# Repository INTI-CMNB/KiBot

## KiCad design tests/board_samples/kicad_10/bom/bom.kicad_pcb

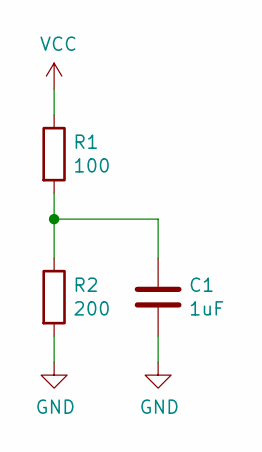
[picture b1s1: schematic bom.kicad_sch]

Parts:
C1: 1uF; C_0805_2012Metric
R1: 100; R_0805_2012Metric
R2: 200; R_0805_2012Metric

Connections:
GND: C1.2, R2.2
unnamed: C1.1, R1.2, R2.1
VCC: R1.1

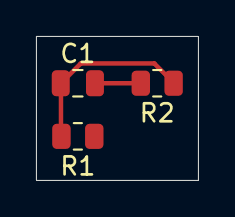
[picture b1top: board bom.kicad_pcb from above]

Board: 2 copper layers, 9.0 x 8.0 mm, 3 parts (0 on the bottom side), 2 nets.
